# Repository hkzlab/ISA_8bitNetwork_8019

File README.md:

# RTL8019AS ISA 8bit Network Card

## Introduction

This is an 8bit reimplementation and repackaging of [Manawyrm's ISA8019](https://github.com/Manawyrm/ISA8019), a NE2000-compatible card for the ISA bus.

Differences from the original version include:
- 8bit only design (significantly more compact than the 16bit version)
- Most of the components are now THT (except EEPROM, Network IC and transformer)

### Disclaimer

I take NO responsibility for what happens if you decide to build and use this card. Your computer might crash, catch fire or be destroyed in other nasty ways.
Also, as this card is mostly based on the work of others, You're encourauged to take what you deem fit from this, and use it in your projects!

Additionally, do **NOT CONTACT Manawyrm FOR SUPPORT**, while this board is derived from their work, it is not their product, please do not waste their time.

## Configuration

The board can work in 3 modes:
- Jumper mode (JP jumper set)
This mode allows for manual configuration of any parameters (I/O address, IRQ, BROM address & size, etc.) manually via jumpers. Refer to the back of the PCB for details. 
- EEPROM mode (also called "Jumperless", no jumpers set)
In this mode, all parameters can be configured via the RSET8019.EXE dos utility and will be stored in the 9364 I²C EEPROM.
- PnP mode
For modern computers and operating systems like Windows 9x or Linux, this mode is ideal. Resource management will be done by the BIOS or OS.

I use this 8bit variant in **Jumper mode** (hard to find an 8bit machine with PnP support...).

### Programming utilities

- [RSET8019.EXE](software/Programming%20utilities/Rset8019.exe) for DOS, can set EEPROM parameters, also includes diagnostic functions
- [pg8019](software/Programming%20utilities/pg8019) for DOS, can initialize EEPROM, set MAC address, vendor/product IDs 

### Drivers

- [MS-DOS packet drivers, modded for 8-bit XT machines](software/Drivers/Crynwr%20packet%20driver%20-%20modified%20for%208bit%20operation)

### UMB Support

Revisions 2.4 onward support SRAM chips (e.g. AS6C4008) on the boot ROM slot by correctly bridging J11.

```text
J11 setting, ISA edge connector looking DOWN
EPROM
    | .
    | |
    . |
    
SRAM
    . |
    | |
    | .
```

This is not yet tested by me, but is reported working by modifying a previous revision. Reference this [issue](https://github.com/hkzlab/ISA_8bitNetwork_8019/issues/2).

If you wish to use a SRAM chip for UMB support in previous revisions, cut the traces that go to pin 29 and 31 of the boot ROM, and invert them (connect the trace that went to 29 to pin 31, and vice-versa).

The RTL2UMB software can be found in [this](https://forum.vcfed.org/index.php?threads/pc-dos-3-2-for-5150.78476/) thread.

## Bill of Materials

You can use [LCSC](https://lcsc.com) to source most of the ICs.

- U1: RTL8019AS
- U2: AT93C46DN
- T1: 13F-39MNL
- J2: C133529 CKMTW
- Y1: 20Mhz HC49 crystal
- C9, C9: 20pF ceramic capacitor
- C1,C3-7,C12,C15: 100nF ceramic capacitors
- C2, C16: 10uF/25v electrolytic or ceramic capacitors
- C10-14: 1nF ceramic capacitors
- R4,R5: 1k resistors
- R6-22: 10k resistors
- R3: 200ohm resistor
- R2: 1M resistor
- FB1: Ferrite bead
- ISA bracket: Keystone 9202-1, plus screws. This bracket is made for ISA modems, the hole will be slightly wider than an RJ45 socket.

## Known Issues

- Revision 2.3 has only minor changes, but has not yet been tested by me. Reports are welcome.
- I received a report of this board not allowing Sergey's Micro8088 to boot **unless the IRQ6 line is cut** on the network card. I have not been to reproduce this (maybe because I'm using a terminated backplane?), as the builds I completed are working fine on my Micro8088 cards, but be aware in case you incur in the same issue. **Revision 2.3 keeps IRQ lines 6 and 7, but makes them jumperable and by default disconnected**, so if you have that revision, this should no longer be an issue.

The picture above shows where to cut to isolate IRQ6 in case you suffer the described issue. The trace is located on the backside of the PCB.

## Credits

- Thanks to [Manawyrm](https://github.com/Manawyrm/ISA8019) for the original project

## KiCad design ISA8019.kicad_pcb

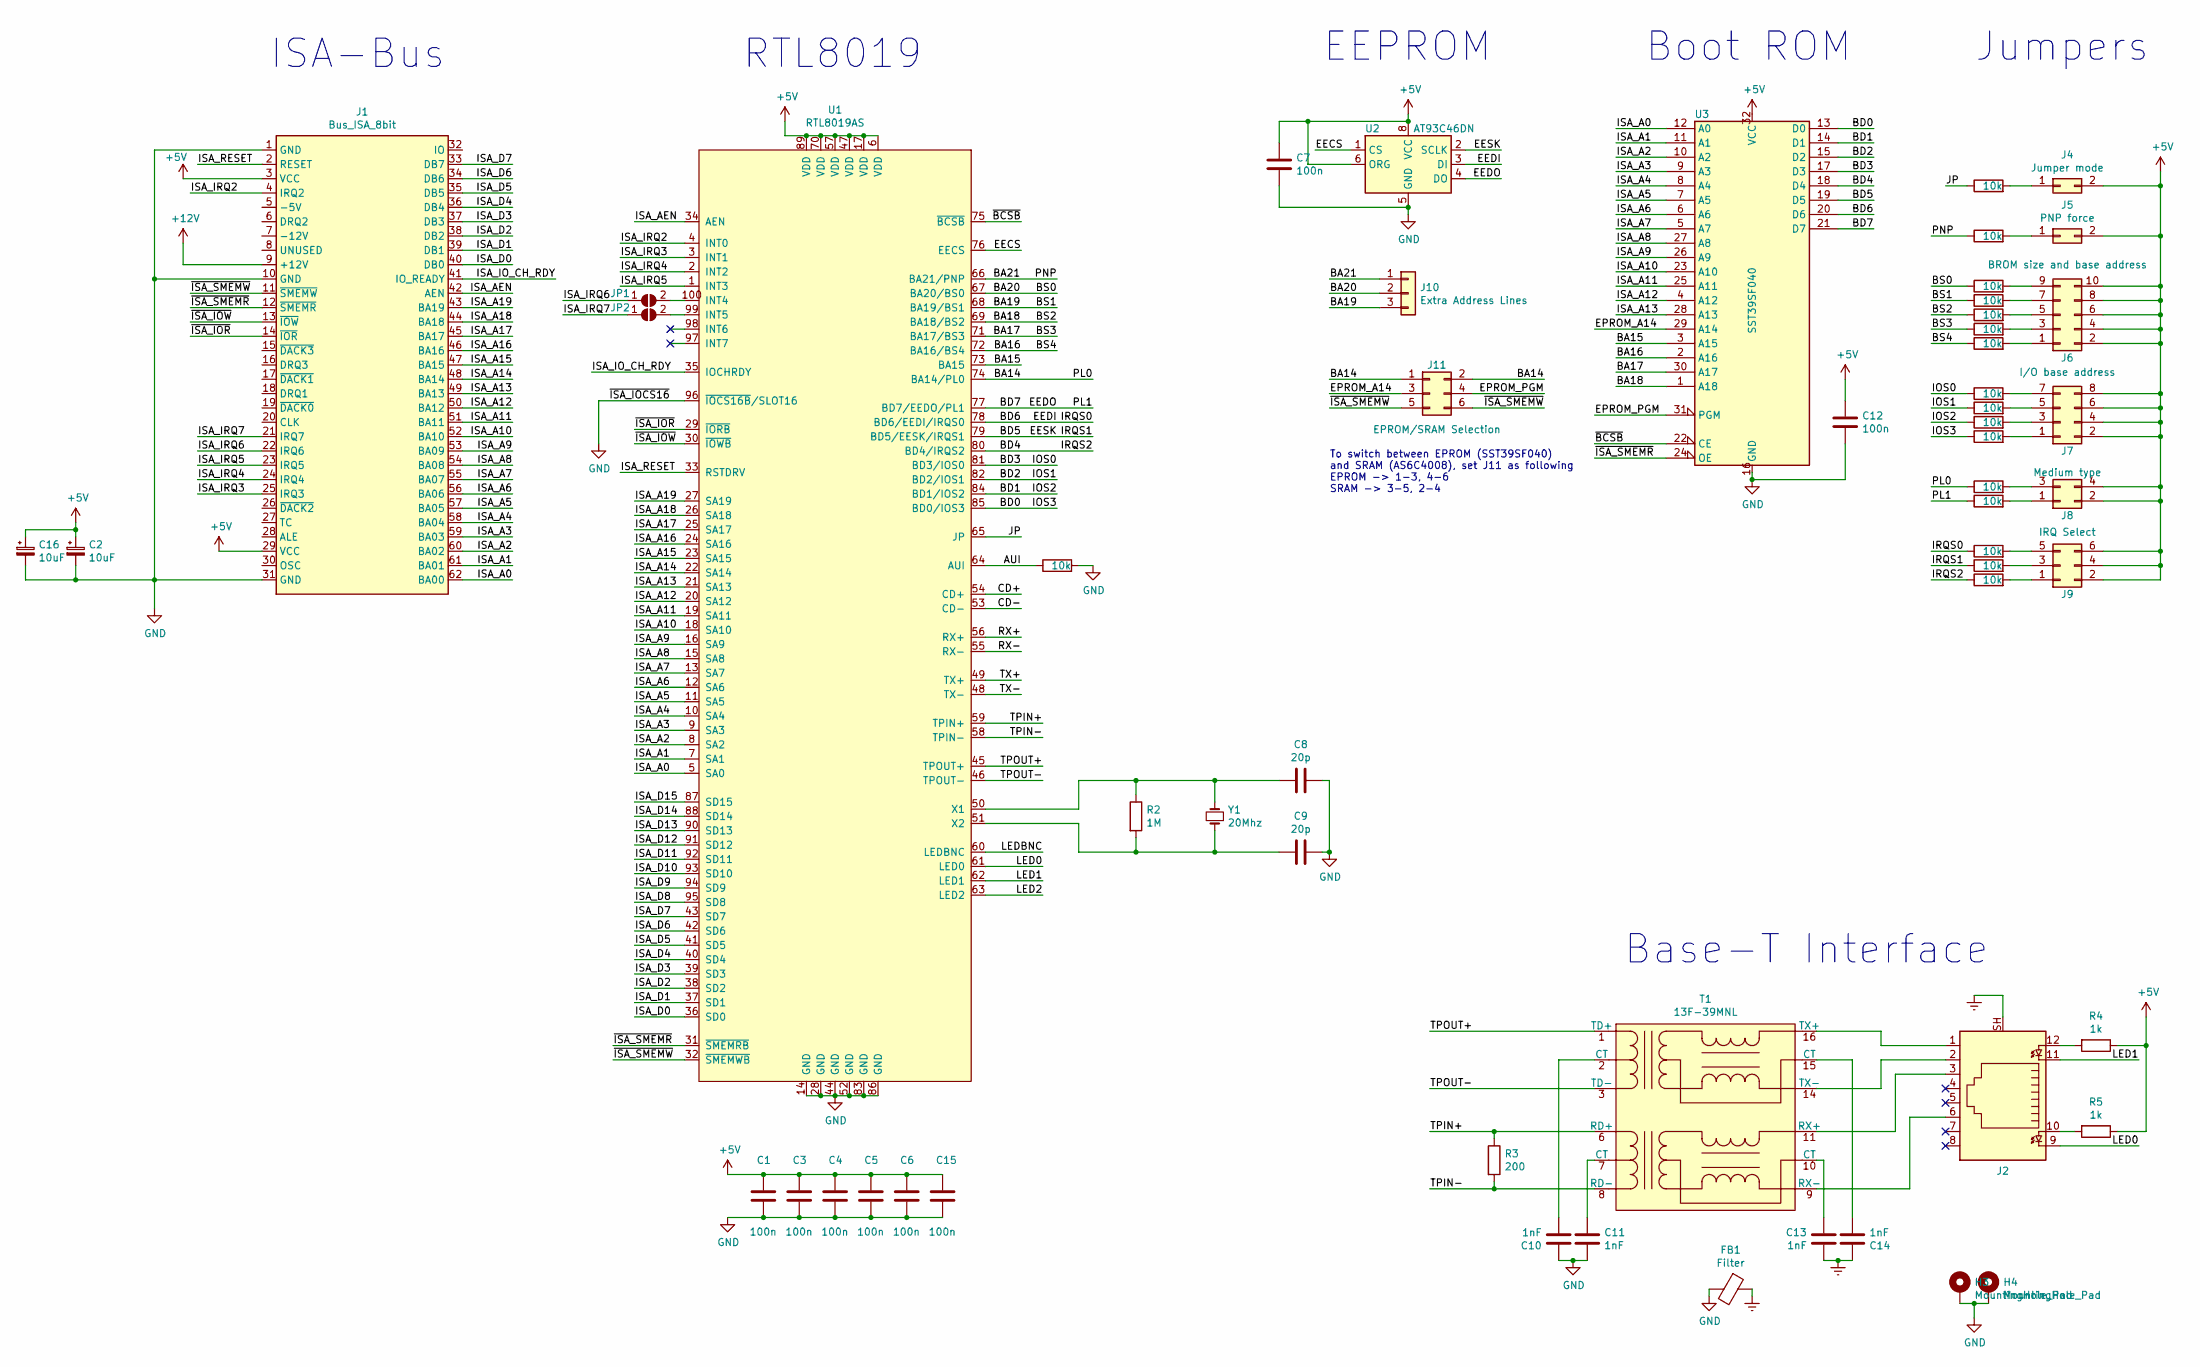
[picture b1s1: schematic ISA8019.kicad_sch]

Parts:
C1, C3, C4, C5, C6, C7, C12, C15: 100n; C_Disc_D6.0mm_W2.5mm_P5.00mm
C2, C16: 10uF; CP_Radial_D5.0mm_P2.50mm
C8: 20p; C_Disc_D5.0mm_W2.5mm_P2.50mm
C9: 20p; C_Disc_D5.0mm_W2.5mm_P2.50mm; LCSC C1554
C10, C11, C13, C14: 1nF; C_Disc_D6.0mm_W2.5mm_P5.00mm
FB1: Filter; L_Axial_L5.3mm_D2.2mm_P10.16mm_Horizontal_Vishay_IM-1; LCSC C1017
H3, H4: MountingHole_Pad; MountingHole_3.2mm_M3_Pad_Via
J1: Bus_ISA_8bit; Conn_Edge_PCB_ISA8
J2: 8P8C_Shielded; 8P8C_yellow_green_Ckmtw_C133529
J4: Jumper mode; PinHeader_2x01_P2.54mm_Vertical
J5: PNP force; PinHeader_2x01_P2.54mm_Vertical
J6: BROM size and base address; PinHeader_2x05_P2.54mm_Vertical
J7: I/O base address; PinHeader_2x04_P2.54mm_Vertical
J8: Medium type; PinHeader_2x02_P2.54mm_Vertical
J9: IRQ Select; PinHeader_2x03_P2.54mm_Vertical
J10: Extra Address Lines; PinHeader_1x03_P2.54mm_Vertical
J11: EPROM/SRAM Selection; PinHeader_2x03_P2.54mm_Vertical
JP1, JP2: IRQ6_Jumper; SolderJumper-2_P1.3mm_Open_RoundedPad1.0x1.5mm
R2: 1M; R_Axial_DIN0207_L6.3mm_D2.5mm_P10.16mm_Horizontal
R3: 200; R_Axial_DIN0207_L6.3mm_D2.5mm_P10.16mm_Horizontal
R4, R5: 1k; R_Axial_DIN0207_L6.3mm_D2.5mm_P10.16mm_Horizontal
R6, R7, R8, R9, R10, R11, R12, R13, R14, R15, R16, R17, R18, R19, R20, R21, R22: 10k; R_Axial_DIN0207_L6.3mm_D2.5mm_P10.16mm_Horizontal
T1: 13F-39MNL; SOIC-16W-12_7.5x10.3mm_P1.27mm; LCSC C115949
U1: RTL8019AS; LQFP-14x20mm_P0.5mm; LCSC C10016
U2: AT93C46DN; SOIC-8_3.9x4.9mm_P1.27mm; LCSC C6499
U3: SST39SF040; DIP-32_W15.24mm_Socket
Y1: 20Mhz; Crystal_HC49-4H_Vertical

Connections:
+5V: C1.1, C2.1, C3.1, C4.1, C5.1, C6.1, C7.1, C12.1, C15.1, C16.1, J1.3 (VCC), J1.29 (VCC), J4.2, J5.2, J6.2, J6.4, J6.6, J6.8, J6.10, J7.2, J7.4, J7.6, J7.8, J8.2, J8.4, J9.2, J9.4, J9.6, R4.1, R5.1, U1.6 (VDD), U1.17 (VDD), U1.47 (VDD), U1.57 (VDD), U1.70 (VDD), U1.89 (VDD), U2.6 (ORG), U2.8 (VCC), U3.32 (VCC)
+12V: J1.9 (+12V)
/AUI: R6.1, U1.64 (AUI)
/BA14: J11.1, J11.2, R18.1, U1.74 (BA14/PL0)
/BA15: U1.73 (BA15), U3.3 (A15)
/BA16: R13.1, U1.72 (BA16/BS4), U3.2 (A16)
/BA17: R12.1, U1.71 (BA17/BS3), U3.30 (A17)
/BA18: R11.1, U1.69 (BA18/BS2), U3.1 (A18)
/BA19: J10.3, R10.1, U1.68 (BA19/BS1)
/BA20: J10.2, R9.1, U1.67 (BA20/BS0)
/BA21: J10.1, R8.1, U1.66 (BA21/PNP)
/BD0: R17.1, U1.85 (BD0/IOS3), U3.13 (D0)
/BD1: R16.1, U1.84 (BD1/IOS2), U3.14 (D1)
/BD2: R15.1, U1.82 (BD2/IOS1), U3.15 (D2)
/BD3: R14.1, U1.81 (BD3/IOS0), U3.17 (D3)
/BD4: R22.1, U1.80 (BD4/IRQS2), U3.18 (D4)
/BD5: R21.1, U1.79 (BD5/EESK/IRQS1), U2.2 (SCLK), U3.19 (D5)
/BD6: R20.1, U1.78 (BD6/EEDI/IRQS0), U2.3 (DI), U3.20 (D6)
/BD7: R19.1, U1.77 (BD7/EEDO/PL1), U2.4 (DO), U3.21 (D7)
/CD+: U1.54 (CD+)
/CD-: U1.53 (CD-)
/EECS: U1.76 (EECS), U2.1 (CS)
/EPROM_A14: J11.3, U3.29 (A14)
/EPROM_PGM: J11.4, U3.31 (PGM)
/ISA_A0: J1.62 (BA00), U1.5 (SA0), U3.12 (A0)
/ISA_A1: J1.61 (BA01), U1.7 (SA1), U3.11 (A1)
/ISA_A2: J1.60 (BA02), U1.8 (SA2), U3.10 (A2)
/ISA_A3: J1.59 (BA03), U1.9 (SA3), U3.9 (A3)
/ISA_A4: J1.58 (BA04), U1.10 (SA4), U3.8 (A4)
/ISA_A5: J1.57 (BA05), U1.11 (SA5), U3.7 (A5)
/ISA_A6: J1.56 (BA06), U1.12 (SA6), U3.6 (A6)
/ISA_A7: J1.55 (BA07), U1.13 (SA7), U3.5 (A7)
/ISA_A8: J1.54 (BA08), U1.15 (SA8), U3.27 (A8)
/ISA_A9: J1.53 (BA09), U1.16 (SA9), U3.26 (A9)
/ISA_A10: J1.52 (BA10), U1.18 (SA10), U3.23 (A10)
/ISA_A11: J1.51 (BA11), U1.19 (SA11), U3.25 (A11)
/ISA_A12: J1.50 (BA12), U1.20 (SA12), U3.4 (A12)
/ISA_A13: J1.49 (BA13), U1.21 (SA13), U3.28 (A13)
/ISA_A14: J1.48 (BA14), U1.22 (SA14)
/ISA_A15: J1.47 (BA15), U1.23 (SA15)
/ISA_A16: J1.46 (BA16), U1.24 (SA16)
/ISA_A17: J1.45 (BA17), U1.25 (SA17)
/ISA_A18: J1.44 (BA18), U1.26 (SA18)
/ISA_A19: J1.43 (BA19), U1.27 (SA19)
/ISA_AEN: J1.42 (AEN), U1.34 (AEN)
/ISA_D0: J1.40 (DB0), U1.36 (SD0)
/ISA_D1: J1.39 (DB1), U1.37 (SD1)
/ISA_D2: J1.38 (DB2), U1.38 (SD2)
/ISA_D3: J1.37 (DB3), U1.39 (SD3)
/ISA_D4: J1.36 (DB4), U1.40 (SD4)
/ISA_D5: J1.35 (DB5), U1.41 (SD5)
/ISA_D6: J1.34 (DB6), U1.42 (SD6)
/ISA_D7: J1.33 (DB7), U1.43 (SD7)
/ISA_D8: U1.95 (SD8)
/ISA_D9: U1.94 (SD9)
/ISA_D10: U1.93 (SD10)
/ISA_D11: U1.92 (SD11)
/ISA_D12: U1.91 (SD12)
/ISA_D13: U1.90 (SD13)
/ISA_D14: U1.88 (SD14)
/ISA_D15: U1.87 (SD15)
/ISA_IO_CH_RDY: J1.41 (IO_READY), U1.35 (IOCHRDY)
/ISA_IRQ2: J1.4 (IRQ2), U1.4 (INT0)
/ISA_IRQ3: J1.25 (IRQ3), U1.3 (INT1)
/ISA_IRQ4: J1.24 (IRQ4), U1.2 (INT2)
/ISA_IRQ5: J1.23 (IRQ5), U1.1 (INT3)
/ISA_IRQ6: J1.22 (IRQ6), JP1.1 (A)
/ISA_IRQ7: J1.21 (IRQ7), JP2.1 (A)
/ISA_RESET: J1.2 (RESET), U1.33 (RSTDRV)
/JP: R7.1, U1.65 (JP)
/LED0: J2.9, U1.61 (LED0)
/LED1: J2.11, U1.62 (LED1)
/LED2: U1.63 (LED2)
/LEDBNC: U1.60 (LEDBNC)
/RX+: U1.56 (RX+)
/RX-: U1.55 (RX-)
/TPIN+: R3.1, T1.6 (RD+), U1.59 (TPIN+)
/TPIN-: R3.2, T1.8 (RD-), U1.58 (TPIN-)
/TPOUT+: T1.1 (TD+), U1.45 (TPOUT+)
/TPOUT-: T1.3 (TD-), U1.46 (TPOUT-)
/TX+: U1.49 (TX+)
/TX-: U1.48 (TX-)
/~BCSB: U1.75 (~BCSB), U3.22 (CE)
/~ISA_IOR: J1.14 (~IOR), U1.29 (~IORB)
/~ISA_IOW: J1.13 (~IOW), U1.30 (~IOWB)
/~ISA_SMEMR: J1.12 (~SMEMR), U1.31 (~SMEMRB), U3.24 (OE)
/~ISA_SMEMW: J1.11 (~SMEMW), J11.5, J11.6, U1.32 (~SMEMWB)
Earth: C13.2, C14.1, FB1.1, J2.SH
GND: C1.2, C2.2, C3.2, C4.2, C5.2, C6.2, C7.2, C8.1, C9.1, C10.1, C11.2, C12.2, C15.2, C16.2, FB1.2, H3.1, H4.1, J1.1 (GND), J1.10 (GND), J1.31 (GND), R6.2, U1.14 (GND), U1.28 (GND), U1.44 (GND), U1.52 (GND), U1.83 (GND), U1.86 (GND), U1.96 (~IOCS16B/SLOT16), U2.5 (GND), U3.16 (GND)
unnamed: C8.2, R2.1, U1.50 (X1), Y1.2
unnamed: C9.2, R2.2, U1.51 (X2), Y1.1
unnamed: C10.2, T1.2 (CT)
unnamed: C11.1, T1.7 (CT)
unnamed: C13.1, T1.10 (CT)
unnamed: C14.2, T1.15 (CT)
unnamed: J2.1, T1.16 (TX+)
unnamed: J2.2, T1.14 (TX-)
unnamed: J2.3, T1.11 (RX+)
unnamed: J2.6, T1.9 (RX-)
unnamed: J2.10, R5.2
unnamed: J2.12, R4.2
unnamed: J4.1, R7.2
unnamed: J5.1, R8.2
unnamed: J6.1, R13.2
unnamed: J6.3, R12.2
unnamed: J6.5, R11.2
unnamed: J6.7, R10.2
unnamed: J6.9, R9.2
unnamed: J7.1, R17.2
unnamed: J7.3, R16.2
unnamed: J7.5, R15.2
unnamed: J7.7, R14.2
unnamed: J8.1, R19.2
unnamed: J8.3, R18.2
unnamed: J9.1, R22.2
unnamed: J9.3, R21.2
unnamed: J9.5, R20.2
unnamed: JP1.2 (B), U1.100 (INT4)
unnamed: JP2.2 (B), U1.99 (INT5)

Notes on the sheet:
Jumpers
ISA-Bus
Boot ROM
RTL8019
To switch between EPROM (SST39SF040) and SRAM (AS6C4008), set J11 as following EPROM -> 1-3, 4-6 SRAM -> 3-5, 2-4
Base-T Interface
EEPROM

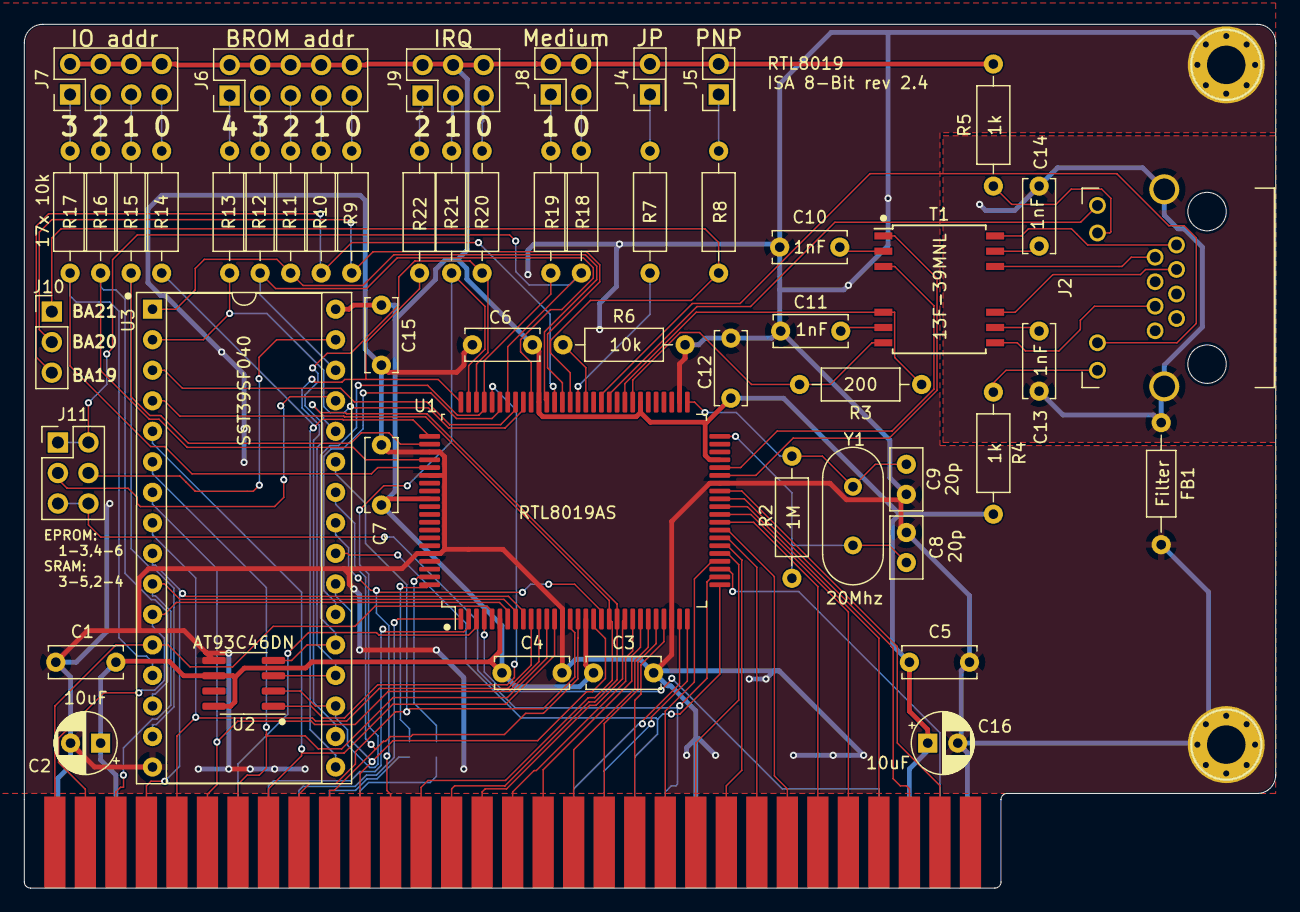
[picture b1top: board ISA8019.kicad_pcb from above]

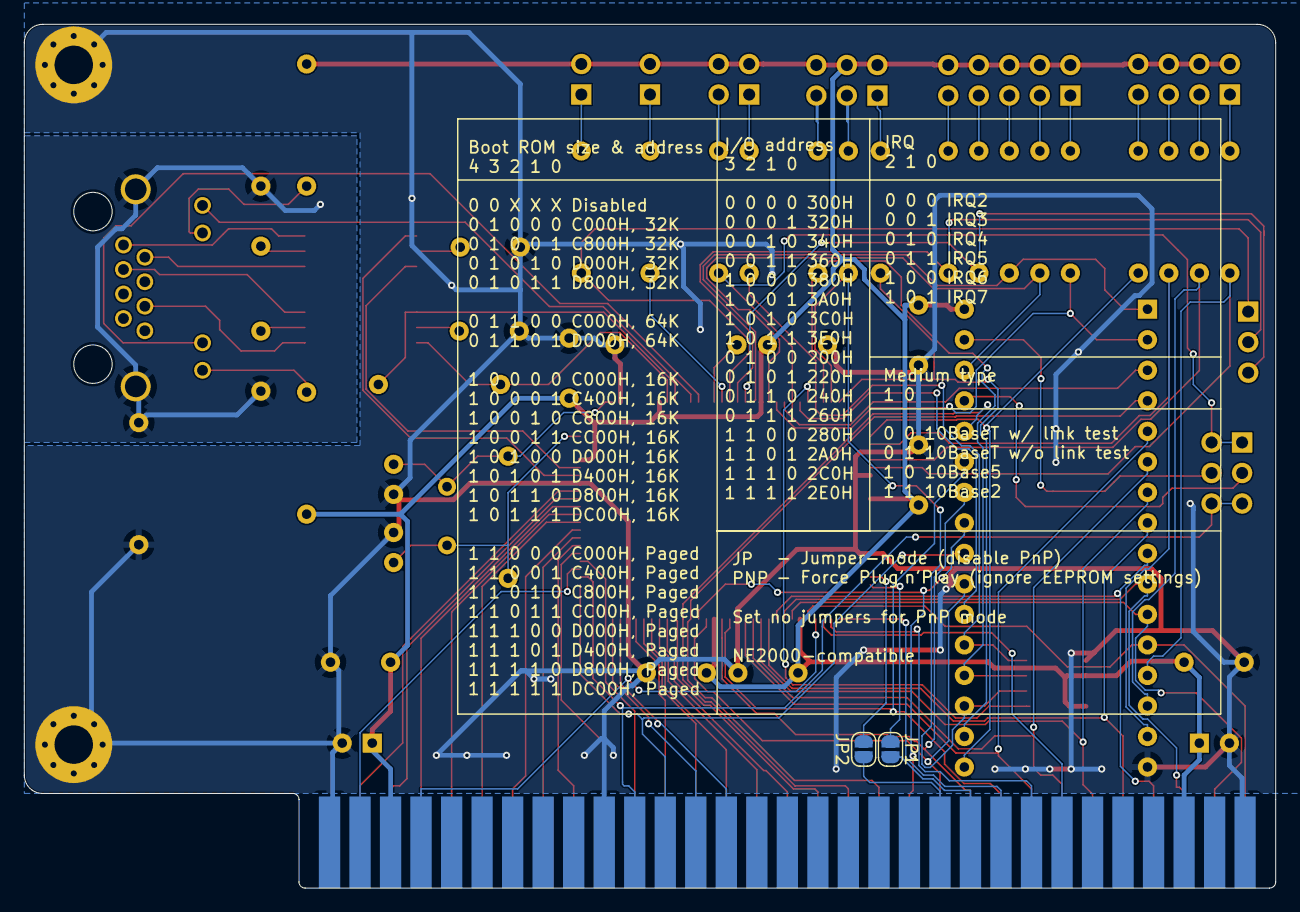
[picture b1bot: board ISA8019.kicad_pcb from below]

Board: 2 copper layers, 104.1 x 71.9 mm, 57 parts (2 on the bottom side), 102 nets.

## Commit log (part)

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2021-03-26 import project
2021-03-26 8 bit network card variant
2021-03-27 Redraw 8 bit board
2021-03-27 cleanup board a bit
2021-03-27 Update board
2021-03-27 Fix top zone fill
2021-03-27 Rev 1 gerbers
2021-04-17 Fix bottom no-net fill
2021-04-17 Add another filter cap
2021-04-17 Adjust board edges
2021-04-17 Update the revision
2021-04-17 Resize board and remove jumper for 16-bit IRQs
2021-04-17 Removed useless pulldown resistor
2021-04-17 Smaller version of the ethernet card
2021-04-17 Redraw fill areas
2021-04-17 Silkscreen adjustments
2021-04-17 Reorganize zones on the PCB
2021-04-24 Added more IRQ options
2021-04-24 Cleanup tracks
2021-04-25 Tweak ground plane a bit
2021-04-27 Add rev 2 gerber
2021-05-11 Upload basic software from Manawyrm's repo
2021-05-12 Update the readme and add pictures
2021-05-12 Resize picture
2021-05-12 Remove rev.1 gerbers
2021-05-12 Fix README
2021-05-25 Add keystone bracket
2021-05-25 Add bracket
2021-05-25 move pcb on sheet
2021-05-25 Slightly move bracket holes for better bracket positioning
2021-05-25 Move net connector slightly forward
2021-05-25 Move mask zone
2021-05-25 Add gerbers for 2.1
2021-06-02 Add rev 2.2, supporting an 30SF040 EPROM, also additional address lines are now broken out
2021-06-02 Fix address BA14/16 ordering to SST39SF040
2021-06-02 Regenerate gerbers
2021-11-09 Update kicad url
2022-07-01 Add revision 2.3 of the board to jumper IRQ6 and 7 and keep them disconnected by default
2022-07-01 Add notes about 2.3 to README
2022-07-01 Further details in README
2022-07-01 Added pic on issue section
2022-07-01 Typo
2022-10-07 Add header to switch between SRAM and EPROM
2022-10-07 Add some descriptive text for J11
2022-10-07 Prepare what will be revision 2.4
2022-10-07 Add Revision 2.4
2022-10-07 Different README
2022-10-07 Better indicatiosn in README
